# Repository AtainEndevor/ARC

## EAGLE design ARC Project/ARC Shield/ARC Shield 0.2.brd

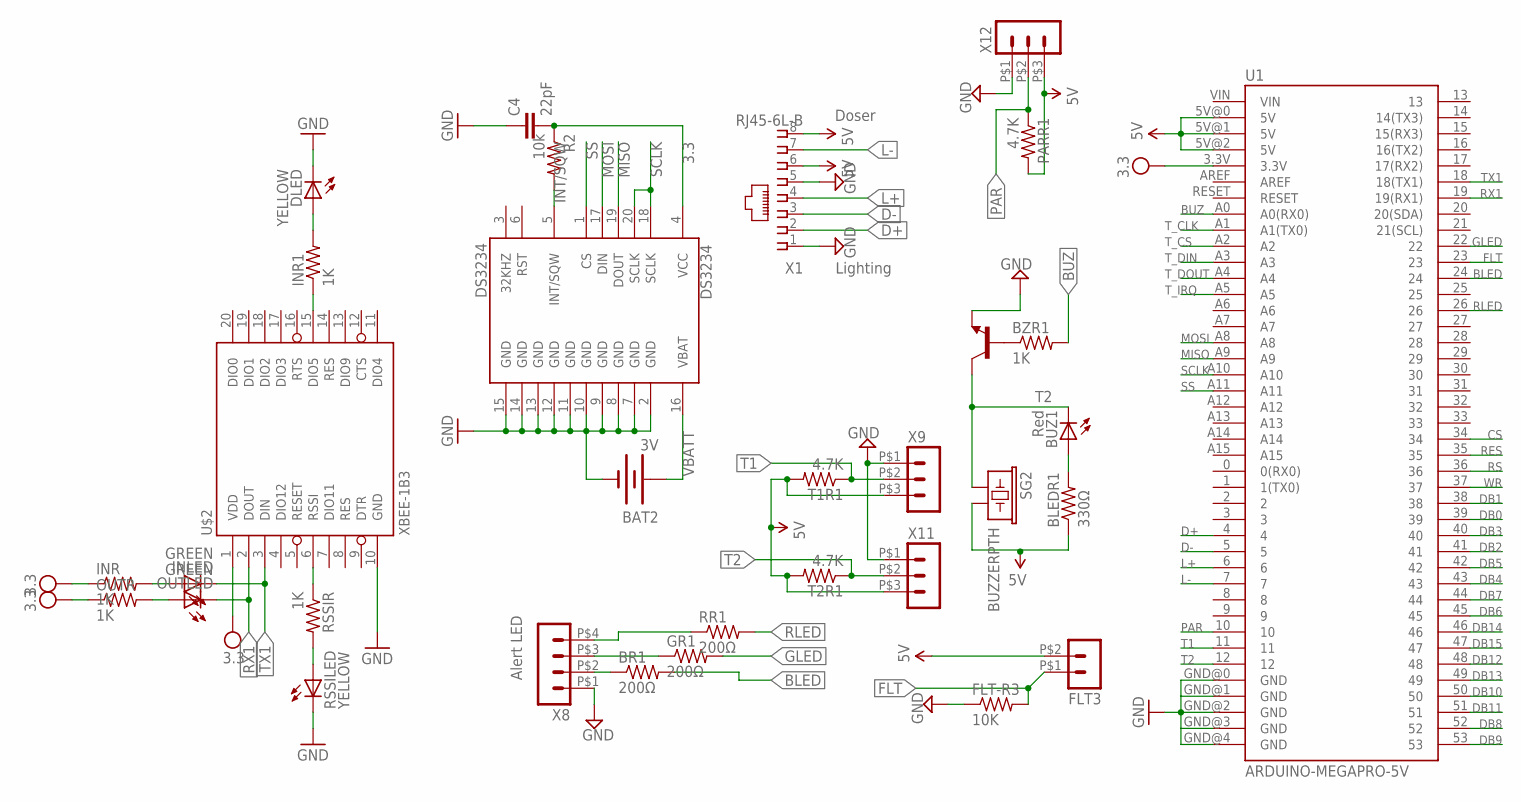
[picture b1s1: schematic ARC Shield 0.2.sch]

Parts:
BAT2: 3V; BATTCON_12MM_CURVED
BLEDR1: 330Ω; 0204/7
BR1: 200Ω; 0204/7
BUZ1: Red; LED3MM
BZR1: 1K; 0204/7
C4: 22pF; C5B3
DLED: YELLOW; LED3MM
DS3234: DS3234
FLT3: HEADER_POS2_43045-0200; 43045-0200
FLT-R3: 10K; 0204/7
GR1: 200Ω; 0204/7
INLED: GREEN; LED3MM
INR, INR1: 1K; 0204/7
OUTLED: GREEN; LED3MM
OUTR: 1K; 0204/7
PARR1: 4.7K; 0204/7
R2: 10k; 0204/7
RR1: 200Ω; 0204/7
RSSILED: YELLOW; LED3MM
RSSIR: 1K; 0204/7
SG2: BUZZERPTH; BUZZER-12MM
T1R1, T2R1: 4.7K; 0204/7
T2: -NPN-TO92; TO92
U1: ARDUINO-MEGAPRO-5V; ARDUINO_MEGA-PRO-5V
U$2: XBEE-1B3; XBEE-SMD
X1: RJ45-6L-B; RJ45-NO-SHIELD
X8: HEADER_POS4_43045-0401; 43045-0400
X9, X11, X12: HEADER_POS3_43650-0300; 43650-0300

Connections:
3.3: C4.2, DS3234.4 (VCC), R2.1, U$2.1 (VDD)
5V: BLEDR1.1, FLT3.P$2 (2), PARR1.2, SG2.- (2), T1R1.2, T2R1.2, U1.5V@0 (5V), U1.5V@1 (5V), U1.5V@2 (5V), X1.6, X1.8, X9.P$3 (3), X11.P$3 (3), X12.P$3 (3)
BLED: BR1.2, U1.24
BUZ: BZR1.2, U1.A0 (A0(RX0))
CS: U1.34
D+: U1.4, X1.2
D-: U1.5, X1.3
DB0: U1.39
DB1: U1.38
DB2: U1.41
DB3: U1.40
DB4: U1.43
DB5: U1.42
DB6: U1.45
DB7: U1.44
DB8: U1.52
DB9: U1.53
DB10: U1.50
DB11: U1.51
DB12: U1.48
DB13: U1.49
DB14: U1.46
DB15: U1.47
FLT: FLT3.P$1 (1), FLT-R3.2, U1.23
GLED: GR1.2, U1.22
GND: BAT2.GND (-), C4.1, DLED.K (C), DS3234.2 (GND), DS3234.7 (GND), DS3234.8 (GND), DS3234.9 (GND), DS3234.10 (GND), DS3234.11 (GND), DS3234.12 (GND), DS3234.13 (GND), DS3234.14 (GND), DS3234.15 (GND), FLT-R3.1, RSSILED.K (C), T2.1 (E), U1.GND@0 (GND), U1.GND@1 (GND), U1.GND@2 (GND), U1.GND@3 (GND), U1.GND@4 (GND), U$2.10 (GND), X1.1, X1.5, X8.P$1 (1), X9.P$1 (1), X11.P$1 (1), X12.P$1 (1)
INT/SQW: DS3234.5 (INT/SQW), R2.2
L+: U1.6, X1.4
L-: U1.7, X1.7
MISO: DS3234.19 (DOUT), U1.A9
MOSI: DS3234.17 (DIN), U1.A8
unnamed: BR1.1, X8.P$2 (2)
unnamed: BUZ1.K (C), SG2.+ (1), T2.3 (C)
unnamed: BZR1.1, T2.2 (B)
unnamed: RSSIR.1, U$2.6 (RSSI)
unnamed: GR1.1, X8.P$3 (3)
unnamed: RSSILED.A, RSSIR.2
unnamed: RR1.1, X8.P$4 (4)
unnamed: INLED.A, INR.2
unnamed: OUTLED.A, OUTR.2
unnamed: DLED.A, INR1.2
unnamed: INR1.1, U$2.15 (DIO5)
unnamed: BLEDR1.2, BUZ1.A
PAR: PARR1.1, U1.10, X12.P$2 (2)
RES: U1.35
RLED: RR1.2, U1.26
RS: U1.36
RX1: OUTLED.K (C), U1.19 (19(RX1)), U$2.2 (DOUT)
SCLK: DS3234.18 (SCLK), DS3234.20 (SCLK), U1.A10
SS: DS3234.1 (CS), U1.A11
T1: T1R1.1, U1.11, X9.P$2 (2)
T2: T2R1.1, U1.12, X11.P$2 (2)
TX1: INLED.K (C), U1.18 (18(TX1)), U$2.3 (DIN)
T_CLK: U1.A1 (A1(TX0))
T_CS: U1.A2
T_DIN: U1.A3
T_DOUT: U1.A4
T_IRQ: U1.A5
VBATT: BAT2.PWR@1 (+), DS3234.16 (VBAT)
VCC: INR.1, OUTR.1, U1.3.3V
WR: U1.37

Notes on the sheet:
Doser
Alert LED
Lighting

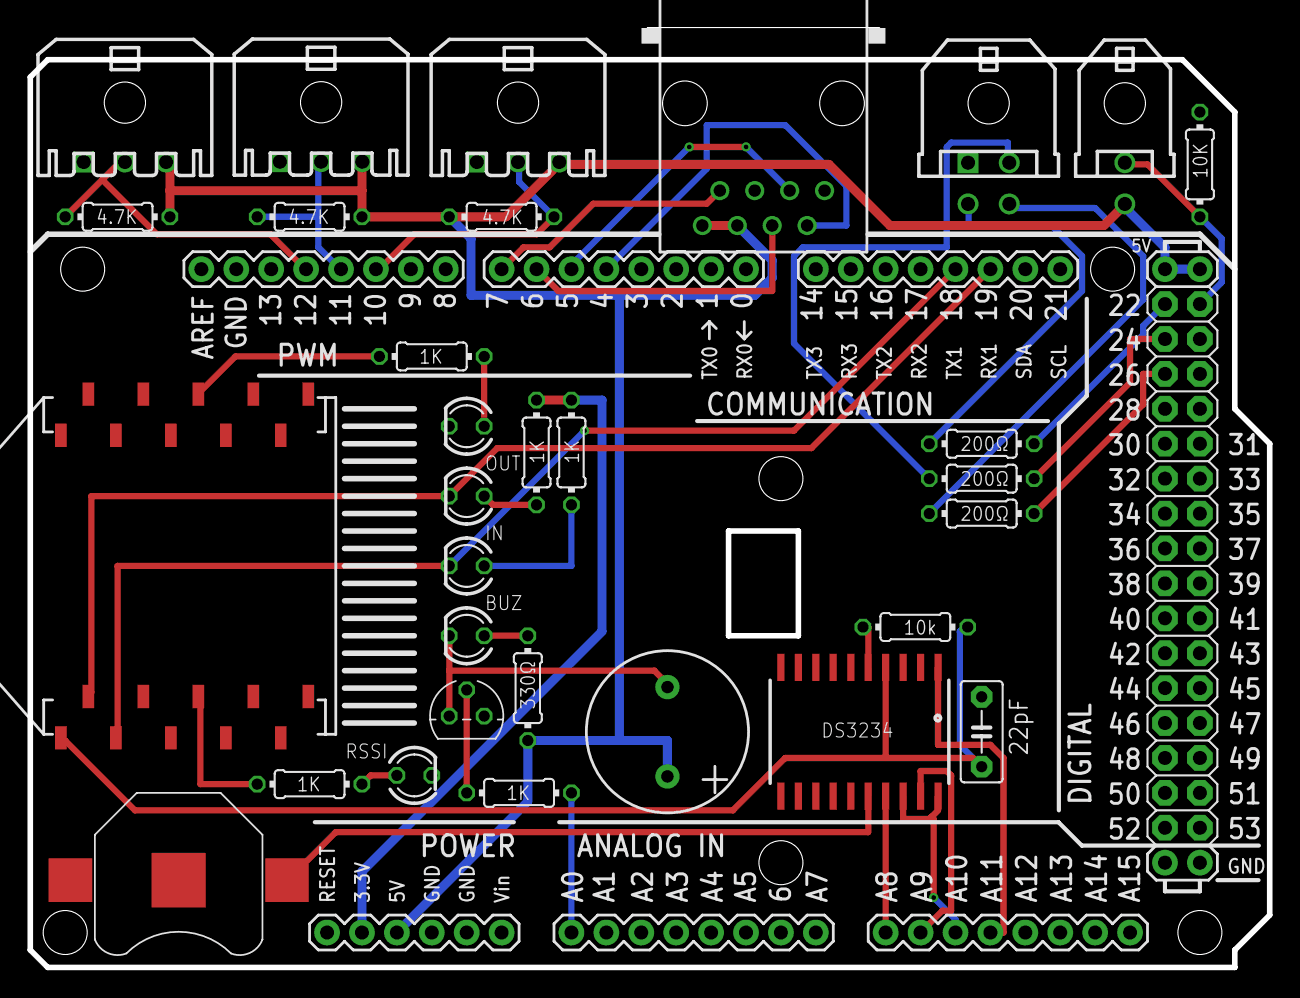
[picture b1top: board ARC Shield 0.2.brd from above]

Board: 2 copper layers, 90.2 x 68.4 mm, 32 parts (0 on the bottom side), 36 nets.

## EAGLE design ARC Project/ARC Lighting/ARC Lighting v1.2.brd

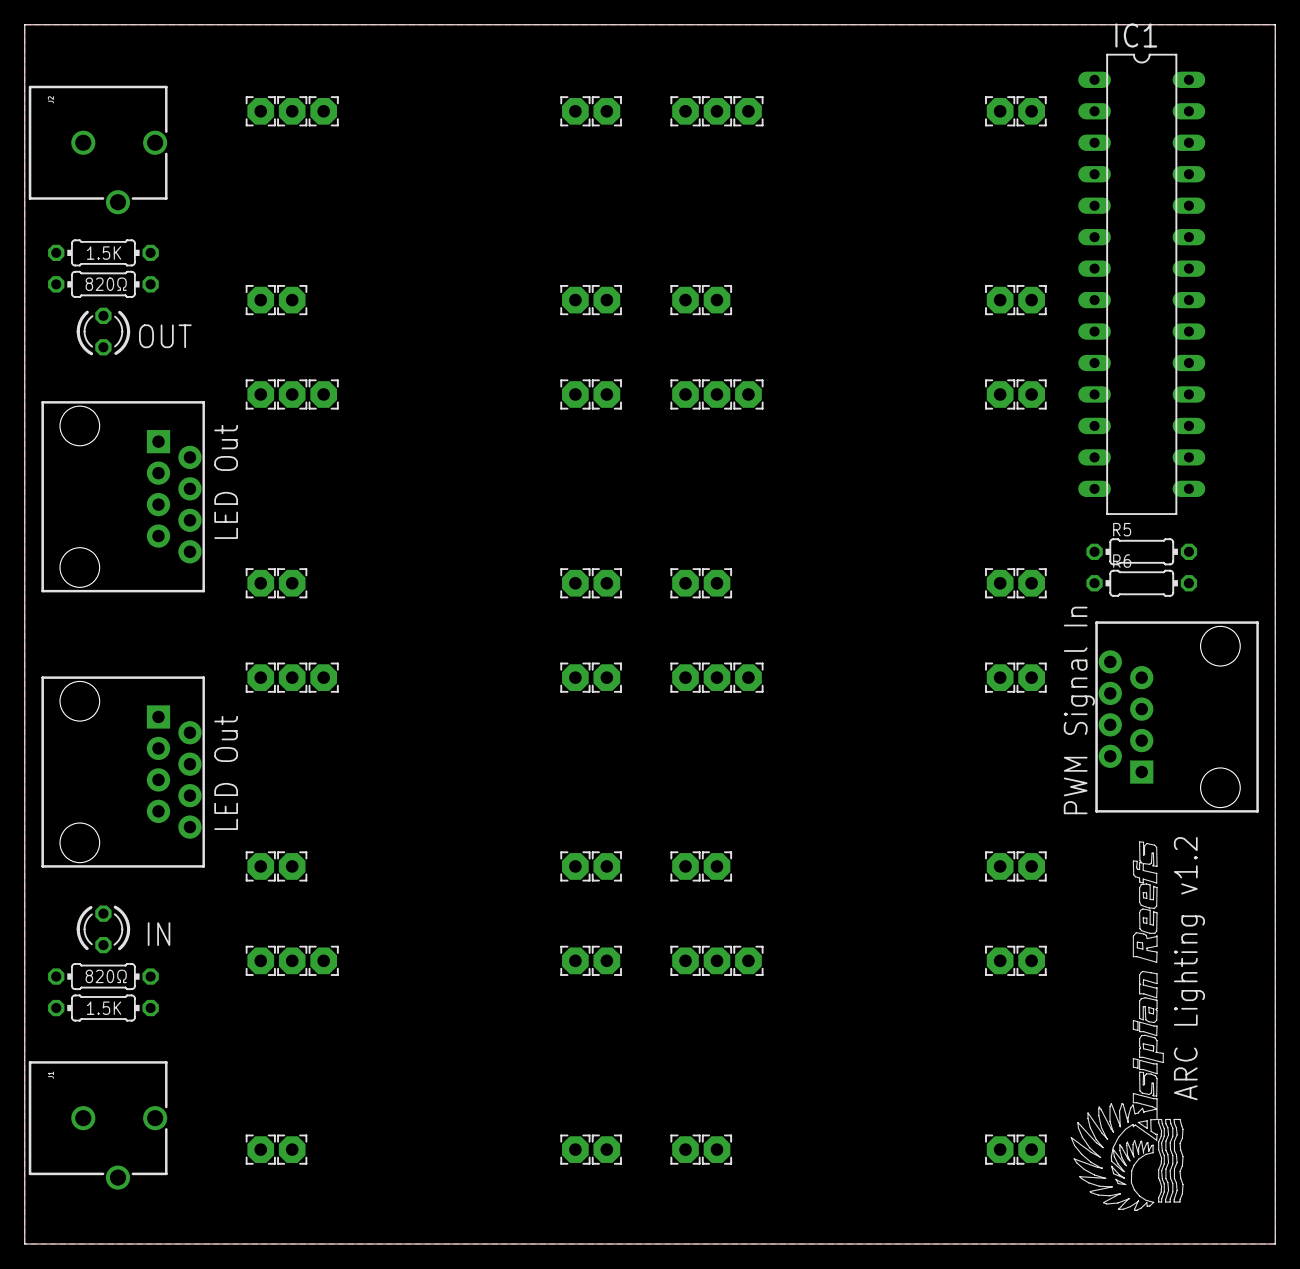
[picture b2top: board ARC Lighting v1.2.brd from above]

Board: 2 copper layers, 100.9 x 98.4 mm, 86 parts (0 on the bottom side), 35 nets, no tracks yet.

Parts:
DIM0, DIM1, DIM2, DIM3, DIM4, DIM5, DIM6, DIM7: 2,15/1,0
I+0, I+1, I+2, I+3, I+4, I+5, I+6, I+7: 2,15/1,0
I-0, I-1, I-2, I-3, I-4, I-5, I-6, I-7: 2,15/1,0
IC1: DIP28
J1, J2: Power; POWER_JACK_PTH_BREAD
LED1, LED2: LED3MM
O+0, O+1, O+2, O+3, O+4, O+5, O+6, O+7: 2,15/1,0
O-0, O-1, O-2, O-3, O-4, O-5, O-6, O-7: 2,15/1,0
R1, R3: 1.5K; 0204/7
R2, R4, R5, R6: 820Ω; 0204/7
U$1, U$2, U$3: RJ45-8PTH; RJ45-8
VIN+0, VIN+1, VIN+2, VIN+3, VIN+4, VIN+5, VIN+6, VIN+7: 2,15/1,0
VIN-0, VIN-1, VIN-2, VIN-3, VIN-4, VIN-5, VIN-6, VIN-7: 2,15/1,0
VOUT+0, VOUT+1, VOUT+2, VOUT+3, VOUT+4, VOUT+5, VOUT+6, VOUT+7: 2,15/1,0
VOUT-0, VOUT-1, VOUT-2, VOUT-3, VOUT-4, VOUT-5, VOUT-6, VOUT-7: 2,15/1,0

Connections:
5V: IC1.19, IC1.21, R6.1
12V: I+0.1, I+1.1, I+2.1, I+3.1, I+4.1, I+5.1, I+6.1, I+7.1, J1.PWR, J2.PWR, VIN+0.1, VIN+1.1, VIN+2.1, VIN+3.1, VIN+4.1, VIN+5.1, VIN+6.1, VIN+7.1
GND: I-0.1, I-1.1, I-2.1, I-3.1, I-4.1, I-5.1, I-6.1, I-7.1, IC1.22, J1.GND, J2.GND, LED1.K, LED2.K, R5.1, VIN-0.1, VIN-1.1, VIN-2.1, VIN-3.1, VIN-4.1, VIN-5.1, VIN-6.1, VIN-7.1
L1+: O+1.1, U$2.5, VOUT+1.1
L2+: O+2.1, U$2.4, VOUT+2.1
L2-: O-2.1, U$2.3, VOUT-2.1
L3+: O+3.1, U$2.2, VOUT+3.1
L3-: O-3.1, U$2.1, VOUT-3.1
L4-: O-4.1, U$1.7, VOUT-4.1
L5+: O+5.1, U$1.4, VOUT+5.1
L5-: O-5.1, U$1.3, VOUT-5.1
L6+: O+6.1, U$1.6, VOUT+6.1
L6-: O-6.1, U$1.5, VOUT-6.1
L7+: O+7.1, U$1.2, VOUT+7.1
L7-: O-7.1, U$1.1, VOUT-7.1
LED0: DIM0.1, IC1.1
LED1: DIM1.1, IC1.2
LED2: DIM2.1, IC1.3
LED3: DIM3.1, IC1.4
LED4: DIM4.1, IC1.5
LED5: DIM5.1, IC1.6
LED6: DIM6.1, IC1.7
LED7: DIM7.1, IC1.8
unnamed: J2.GNDBREAK, R1.1
unnamed: R1.2, R2.1
unnamed: LED2.A, R2.2
unnamed: J1.GNDBREAK, R3.1
unnamed: R3.2, R4.1
unnamed: LED1.A, R4.2
unnamed: IC1.23, R6.2
unnamed: IC1.20, R5.2
unnamed: O+4.1, U$1.8, VOUT+4.1
unnamed: O+0.1, U$2.8, VOUT+0.1
unnamed: O-0.1, U$2.7, VOUT-0.1
unnamed: O-1.1, U$2.6, VOUT-1.1

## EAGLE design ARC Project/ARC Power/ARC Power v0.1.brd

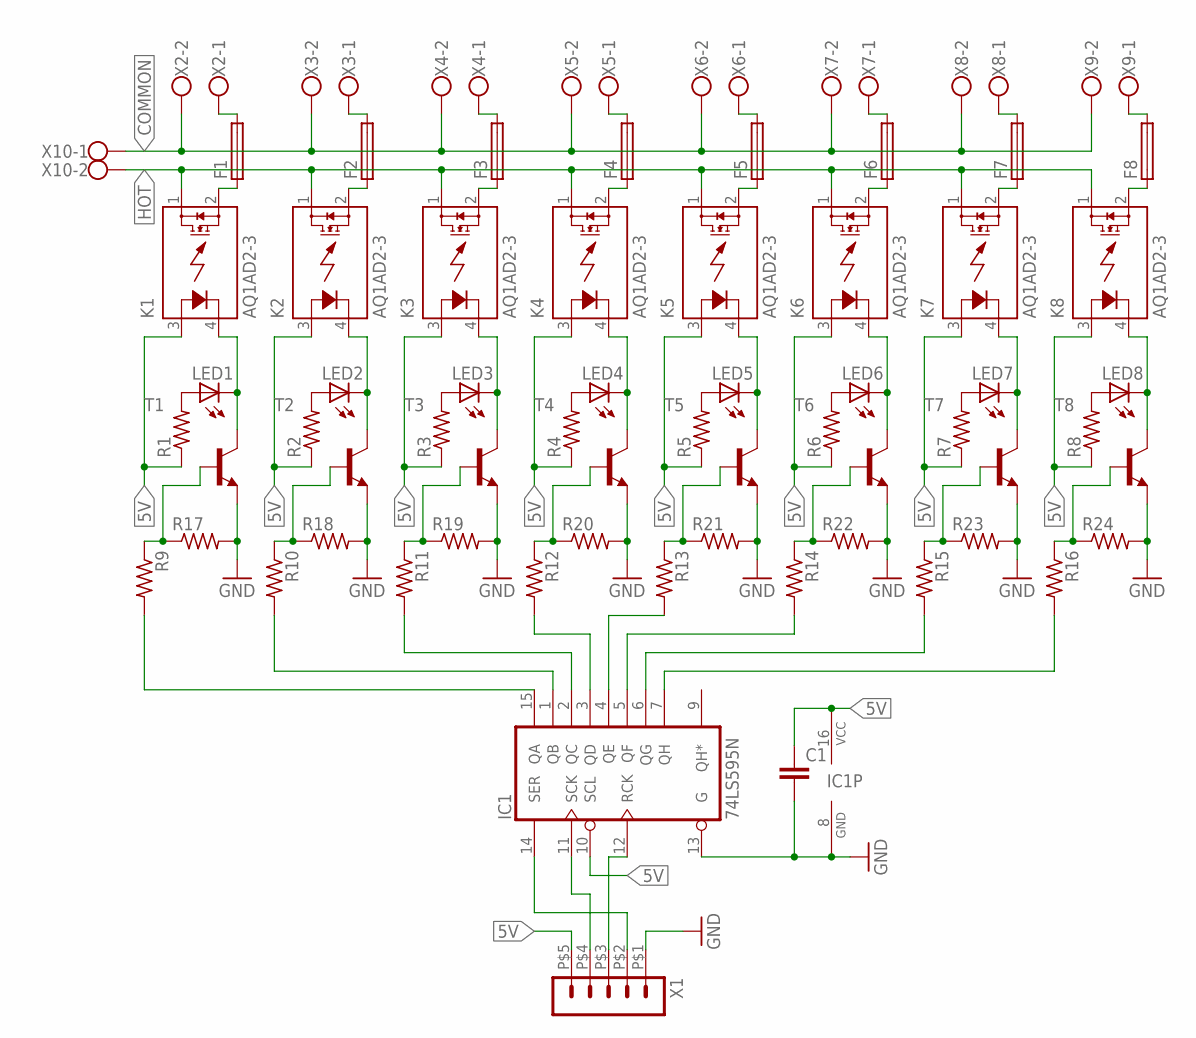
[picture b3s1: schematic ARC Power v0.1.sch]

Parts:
C1: C5/3; C5B3
F1, F2, F3, F4, F5, F6, F7, F8: SH22,5A
IC1: 74LS595N; DIL16
K1, K2, K3, K4, K5, K6, K7, K8: AQ1AD2-3; AQ1
LED1, LED2, LED3, LED4, LED5, LED6, LED7, LED8: LED3MM
R1, R2, R3, R4, R5, R6, R7, R8, R9, R10, R11, R12, R13, R14, R15, R16, R17, R18, R19, R20, R21, R22, R23, R24: R-US_0204/7; 0204/7
T1, T2, T3, T4, T5, T6, T7, T8: -NPN-TO92; TO92
X1: HEADER_POS5_43650-0500; 43650-0500
X2, X3, X4, X5, X6, X7, X8, X9: W237-113
X10: W237-102

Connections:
5V: C1.1, IC1.10 (SCL), IC1.16 (VCC), K1.3 (A), K2.3 (A), K3.3 (A), K4.3 (A), K5.3 (A), K6.3 (A), K7.3 (A), K8.3 (A), R1.1, R2.1, R3.1, R4.1, R5.1, R6.1, R7.1, R8.1, X1.P$5 (5)
COMMON: X2.2, X3.2, X4.2, X5.2, X6.2, X7.2, X8.2, X9.2, X10.1
GND: C1.2, IC1.8 (GND), IC1.13 (G), R17.2, R18.2, R19.2, R20.2, R21.2, R22.2, R23.2, R24.2, T1.1 (E), T2.1 (E), T3.1 (E), T4.1 (E), T5.1 (E), T6.1 (E), T7.1 (E), T8.1 (E), X1.P$1 (1)
HOT: K1.1 (DS1), K2.1 (DS1), K3.1 (DS1), K4.1 (DS1), K5.1 (DS1), K6.1 (DS1), K7.1 (DS1), K8.1 (DS1), X10.2
unnamed: IC1.15 (QA), R9.2
unnamed: IC1.1 (QB), R10.2
unnamed: IC1.2 (QC), R11.2
unnamed: IC1.3 (QD), R12.2
unnamed: IC1.4 (QE), R13.2
unnamed: IC1.5 (QF), R14.2
unnamed: IC1.6 (QG), R15.2
unnamed: IC1.7 (QH), R16.2
unnamed: F1.1, K1.2 (DS2)
unnamed: F1.2, X2.1
unnamed: F2.1, K2.2 (DS2)
unnamed: F2.2, X3.1
unnamed: F3.1, K3.2 (DS2)
unnamed: F3.2, X4.1
unnamed: F4.1, K4.2 (DS2)
unnamed: F4.2, X5.1
unnamed: F5.1, K5.2 (DS2)
unnamed: IC1.14 (SER), X1.P$2 (2)
unnamed: IC1.12 (RCK), X1.P$3 (3)
unnamed: IC1.11 (SCK), X1.P$4 (4)
unnamed: F5.2, X6.1
unnamed: F6.1, K6.2 (DS2)
unnamed: F6.2, X7.1
unnamed: F7.1, K7.2 (DS2)
unnamed: F7.2, X8.1
unnamed: F8.1, K8.2 (DS2)
unnamed: F8.2, X9.1
unnamed: LED1.A, R1.2
unnamed: LED2.A, R2.2
unnamed: LED3.A, R3.2
unnamed: LED4.A, R4.2
unnamed: LED5.A, R5.2
unnamed: LED6.A, R6.2
unnamed: LED7.A, R7.2
unnamed: LED8.A, R8.2
unnamed: K1.4 (K), LED1.K (C), T1.3 (C)
unnamed: K2.4 (K), LED2.K (C), T2.3 (C)
unnamed: K3.4 (K), LED3.K (C), T3.3 (C)
unnamed: K4.4 (K), LED4.K (C), T4.3 (C)
unnamed: K5.4 (K), LED5.K (C), T5.3 (C)
unnamed: K6.4 (K), LED6.K (C), T6.3 (C)
unnamed: K7.4 (K), LED7.K (C), T7.3 (C)
unnamed: K8.4 (K), LED8.K (C), T8.3 (C)
unnamed: R9.1, R17.1, T1.2 (B)
unnamed: R10.1, R18.1, T2.2 (B)
unnamed: R11.1, R19.1, T3.2 (B)
unnamed: R12.1, R20.1, T4.2 (B)
unnamed: R13.1, R21.1, T5.2 (B)
unnamed: R14.1, R22.1, T6.2 (B)
unnamed: R15.1, R23.1, T7.2 (B)
unnamed: R16.1, R24.1, T8.2 (B)

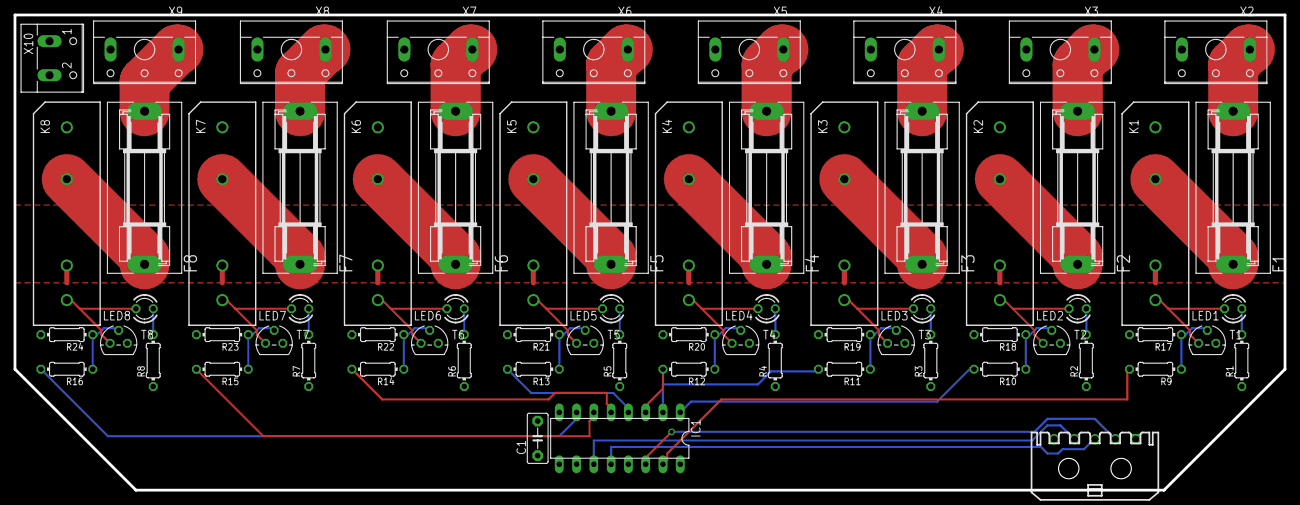
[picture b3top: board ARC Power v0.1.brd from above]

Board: 2 copper layers, 186.7 x 69.9 mm, 68 parts (0 on the bottom side), 55 nets.

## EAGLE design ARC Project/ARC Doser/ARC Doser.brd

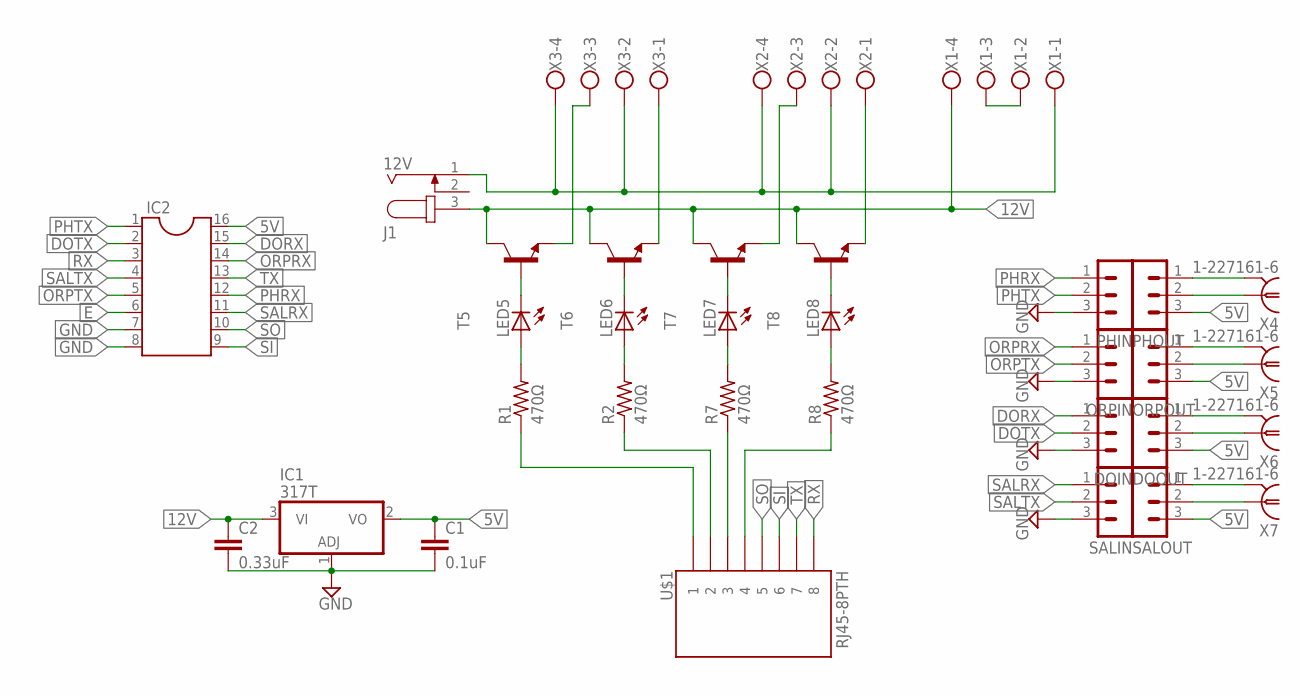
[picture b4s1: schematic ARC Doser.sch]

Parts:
C1: 0.1uF; C5B3
C2: 0.33uF; C5B3
DOIN: MA03-1
DOOUT: MA03-1
IC1: 317T; TO220H
IC2: DIL16
J1: 12V; SPC4077
LED5, LED6, LED7, LED8: LED3MM
ORPIN: MA03-1
ORPOUT: MA03-1
PHIN: MA03-1
PHOUT: MA03-1
R1, R2, R7, R8: 470Ω; 0204/7
SALIN: MA03-1
SALOUT: MA03-1
T5, T6, T7, T8: -NPN-TO92; TO92
U$1: RJ45-8PTH; RJ45-8
X1, X2, X3: W237-4
X4, X5, X6, X7: 1-227161-6; AMP_227161

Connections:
5V: C1.1, DOOUT.3, IC1.2 (VO), IC2.16, ORPOUT.3, PHOUT.3, SALOUT.3
12V: C2.1, IC1.3 (VI), J1.3, T5.3 (C), T6.3 (C), T7.3 (C), T8.3 (C), X1.4
DORX: DOIN.1, IC2.15
DOTX: DOIN.2, IC2.2
E: IC2.6
GND: C1.2, C2.2, DOIN.3, IC1.1 (ADJ), IC2.7, IC2.8, J1.1, ORPIN.3, PHIN.3, SALIN.3, X1.1, X2.2, X2.4, X3.2, X3.4
unnamed: R7.1, U$1.3
unnamed: T5.1 (E), X3.3
unnamed: T6.1 (E), X3.1
unnamed: R8.1, U$1.4
unnamed: LED5.A, R1.2
unnamed: R2.1, U$1.2
unnamed: R1.1, U$1.1
unnamed: T7.1 (E), X2.3
unnamed: T8.1 (E), X2.1
unnamed: PHOUT.1, X4.2
unnamed: ORPOUT.1, X5.2
unnamed: LED5.K (C), T5.2 (B)
unnamed: LED6.A, R2.2
unnamed: DOOUT.1, X6.2
unnamed: SALOUT.1, X7.2
unnamed: PHOUT.2, X4.1
unnamed: X1.2, X1.3
unnamed: ORPOUT.2, X5.1
unnamed: DOOUT.2, X6.1
unnamed: SALOUT.2, X7.1
unnamed: LED6.K (C), T6.2 (B)
unnamed: LED7.A, R7.2
unnamed: LED7.K (C), T7.2 (B)
unnamed: LED8.K (C), T8.2 (B)
unnamed: LED8.A, R8.2
ORPRX: IC2.14, ORPIN.1
ORPTX: IC2.5, ORPIN.2
PHRX: IC2.12, PHIN.1
PHTX: IC2.1, PHIN.2
RX: IC2.3, U$1.8
SALRX: IC2.11, SALIN.1
SALTX: IC2.4, SALIN.2
SI: IC2.9, U$1.6
SO: IC2.10, U$1.5
TX: IC2.13, U$1.7

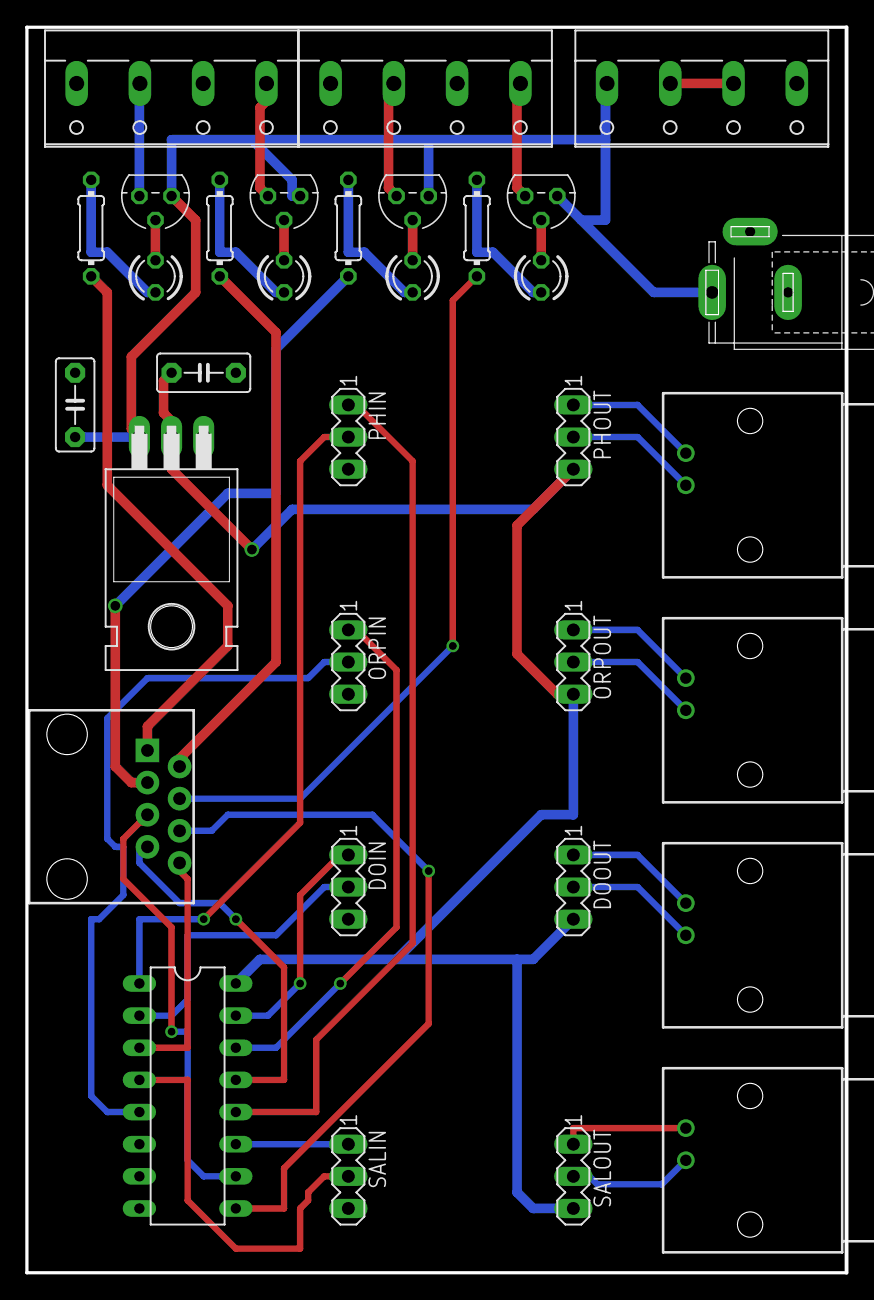
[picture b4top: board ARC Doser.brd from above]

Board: 2 copper layers, 64.8 x 98.4 mm, 33 parts (0 on the bottom side), 40 nets.

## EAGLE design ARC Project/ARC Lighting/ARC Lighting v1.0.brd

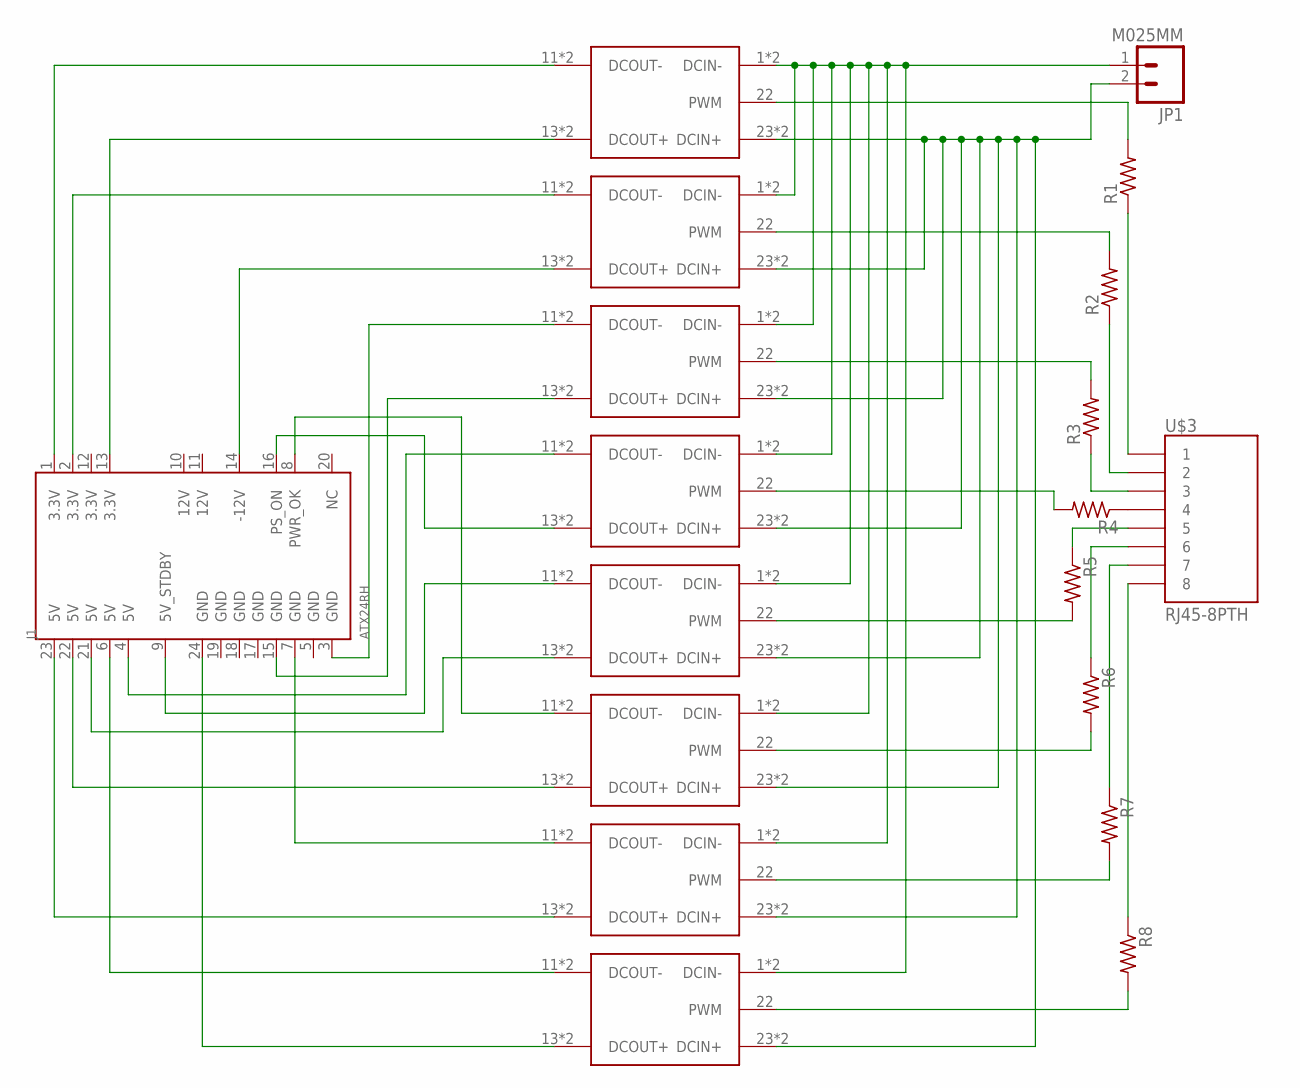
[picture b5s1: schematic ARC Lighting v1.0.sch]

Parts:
J1: ATX24RH; ATX24_RIGHT_ANGLE
JP1: M025MM; SCREWTERMINAL-5MM-2
R1, R2, R3, R4, R5, R6, R7, R8: R-US_0204/7; 0204/7
U$1: 1; LDD_H
U$2: 2; LDD_H
U$3: RJ45-8PTH; RJ45-8
U$4: 3; LDD_H
U$5: 4; LDD_H
U$6: 5; LDD_H
U$7: 6; LDD_H
U$8: 7; LDD_H
U$9: 8; LDD_H

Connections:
unnamed: J1.13 (3.3V), U$1.13 (DCOUT+), U$1.14 (DCOUT+)
unnamed: R2.2, U$2.22 (PWM)
unnamed: R3.2, U$4.22 (PWM)
unnamed: R4.1, U$3.4
unnamed: R8.2, U$9.22 (PWM)
unnamed: R7.2, U$8.22 (PWM)
unnamed: R6.2, U$7.22 (PWM)
unnamed: R5.2, U$6.22 (PWM)
unnamed: J1.1 (3.3V), U$1.11 (DCOUT-), U$1.12 (DCOUT-)
unnamed: JP1.1, U$1.1 (DCIN-), U$1.2 (DCIN-), U$2.1 (DCIN-), U$2.2 (DCIN-), U$4.1 (DCIN-), U$4.2 (DCIN-), U$5.1 (DCIN-), U$5.2 (DCIN-), U$6.1 (DCIN-), U$6.2 (DCIN-), U$7.1 (DCIN-), U$7.2 (DCIN-), U$8.1 (DCIN-), U$8.2 (DCIN-), U$9.1 (DCIN-), U$9.2 (DCIN-)
unnamed: JP1.2, U$1.23 (DCIN+), U$1.24 (DCIN+), U$2.23 (DCIN+), U$2.24 (DCIN+), U$4.23 (DCIN+), U$4.24 (DCIN+), U$5.23 (DCIN+), U$5.24 (DCIN+), U$6.23 (DCIN+), U$6.24 (DCIN+), U$7.23 (DCIN+), U$7.24 (DCIN+), U$8.23 (DCIN+), U$8.24 (DCIN+), U$9.23 (DCIN+), U$9.24 (DCIN+)
unnamed: J1.2 (3.3V), U$2.11 (DCOUT-), U$2.12 (DCOUT-)
unnamed: J1.14 (-12V), U$2.13 (DCOUT+), U$2.14 (DCOUT+)
unnamed: J1.3 (GND), U$4.11 (DCOUT-), U$4.12 (DCOUT-)
unnamed: J1.15 (GND), U$4.13 (DCOUT+), U$4.14 (DCOUT+)
unnamed: J1.4 (5V), U$5.11 (DCOUT-), U$5.12 (DCOUT-)
unnamed: J1.16 (PS_ON), U$5.13 (DCOUT+), U$5.14 (DCOUT+)
unnamed: J1.9 (5V_STDBY), U$6.11 (DCOUT-), U$6.12 (DCOUT-)
unnamed: J1.21 (5V), U$6.13 (DCOUT+), U$6.14 (DCOUT+)
unnamed: J1.8 (PWR_OK), U$7.11 (DCOUT-), U$7.12 (DCOUT-)
unnamed: J1.22 (5V), U$7.13 (DCOUT+), U$7.14 (DCOUT+)
unnamed: J1.7 (GND), U$8.11 (DCOUT-), U$8.12 (DCOUT-)
unnamed: J1.23 (5V), U$8.13 (DCOUT+), U$8.14 (DCOUT+)
unnamed: J1.6 (5V), U$9.11 (DCOUT-), U$9.12 (DCOUT-)
unnamed: J1.24 (GND), U$9.13 (DCOUT+), U$9.14 (DCOUT+)
unnamed: R2.1, U$3.2
unnamed: R3.1, U$3.3
unnamed: R5.1, U$3.5
unnamed: R6.1, U$3.6
unnamed: R7.1, U$3.7
unnamed: R1.1, U$3.1
unnamed: R4.2, U$5.22 (PWM)
unnamed: R8.1, U$3.8
unnamed: R1.2, U$1.22 (PWM)

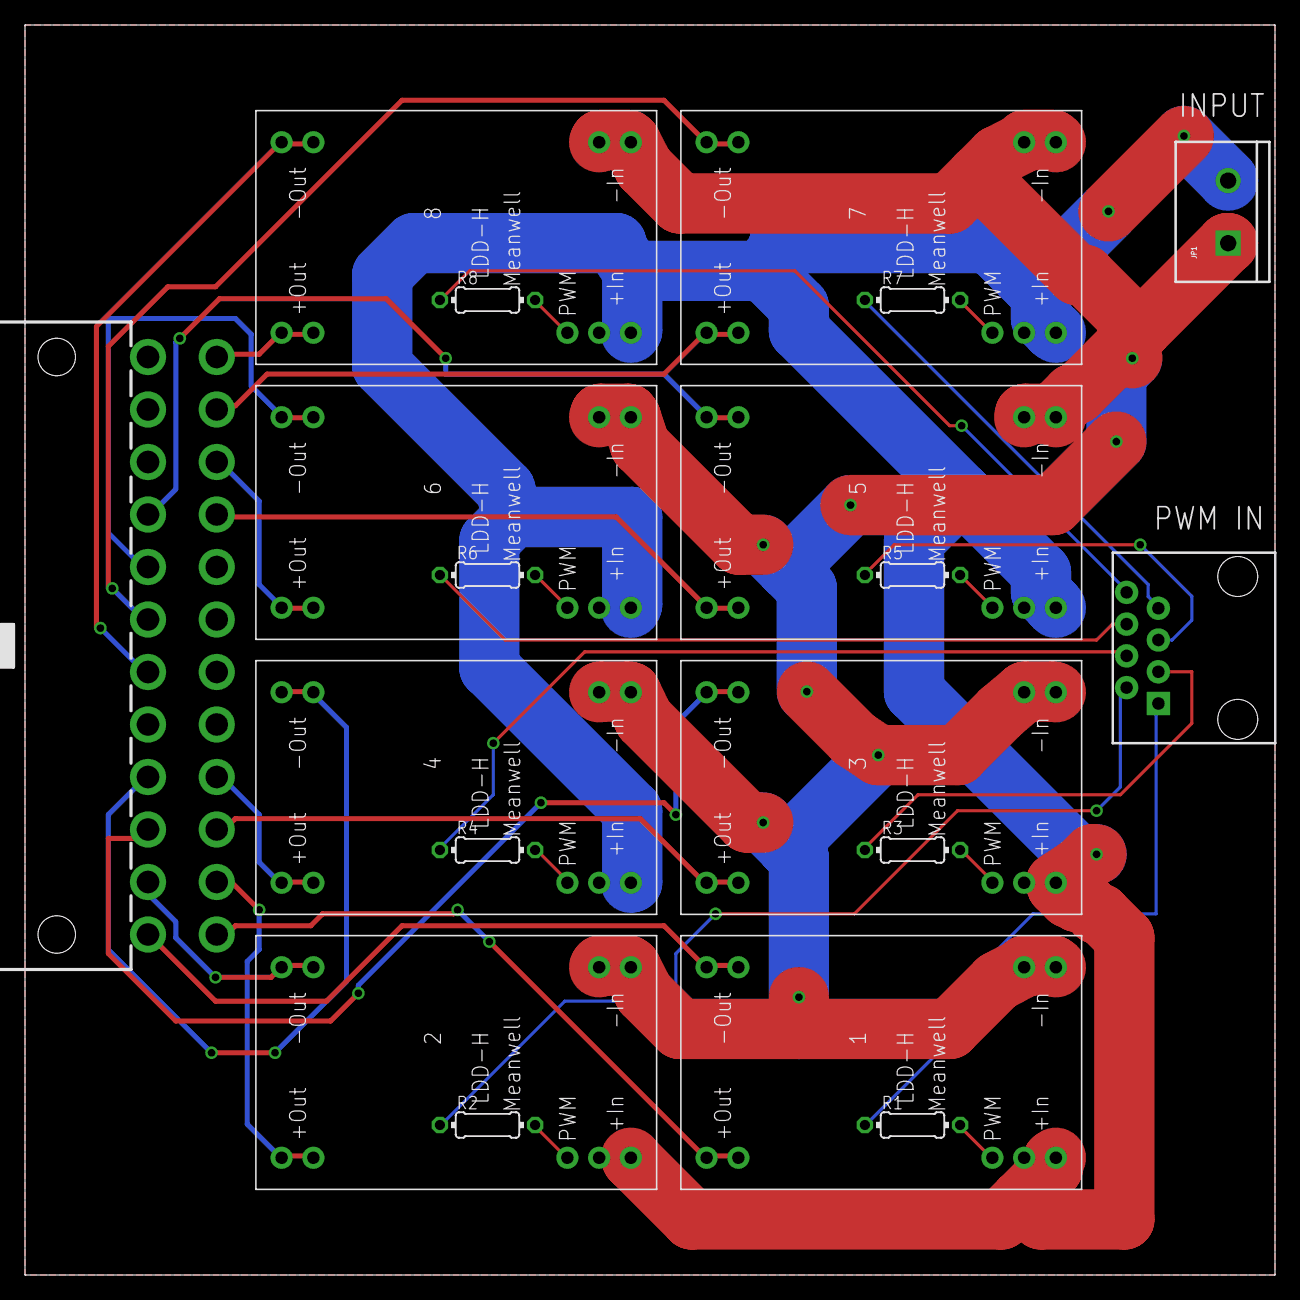
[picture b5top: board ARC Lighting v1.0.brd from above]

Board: 2 copper layers, 100.0 x 100.0 mm, 19 parts (0 on the bottom side), 34 nets.

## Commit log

2020-02-04 Initial Upload

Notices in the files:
parts and their libraries:
SparkFun-Connectors: Licensing: CC v3.0 Share-Alike You are welcome to use this library for commercial purposes.
SparkFun-Aesthetics: Licensing: Creative Commons ShareAlike 4.0 International - https://creativecommons.org/licenses/by-sa/4.0
